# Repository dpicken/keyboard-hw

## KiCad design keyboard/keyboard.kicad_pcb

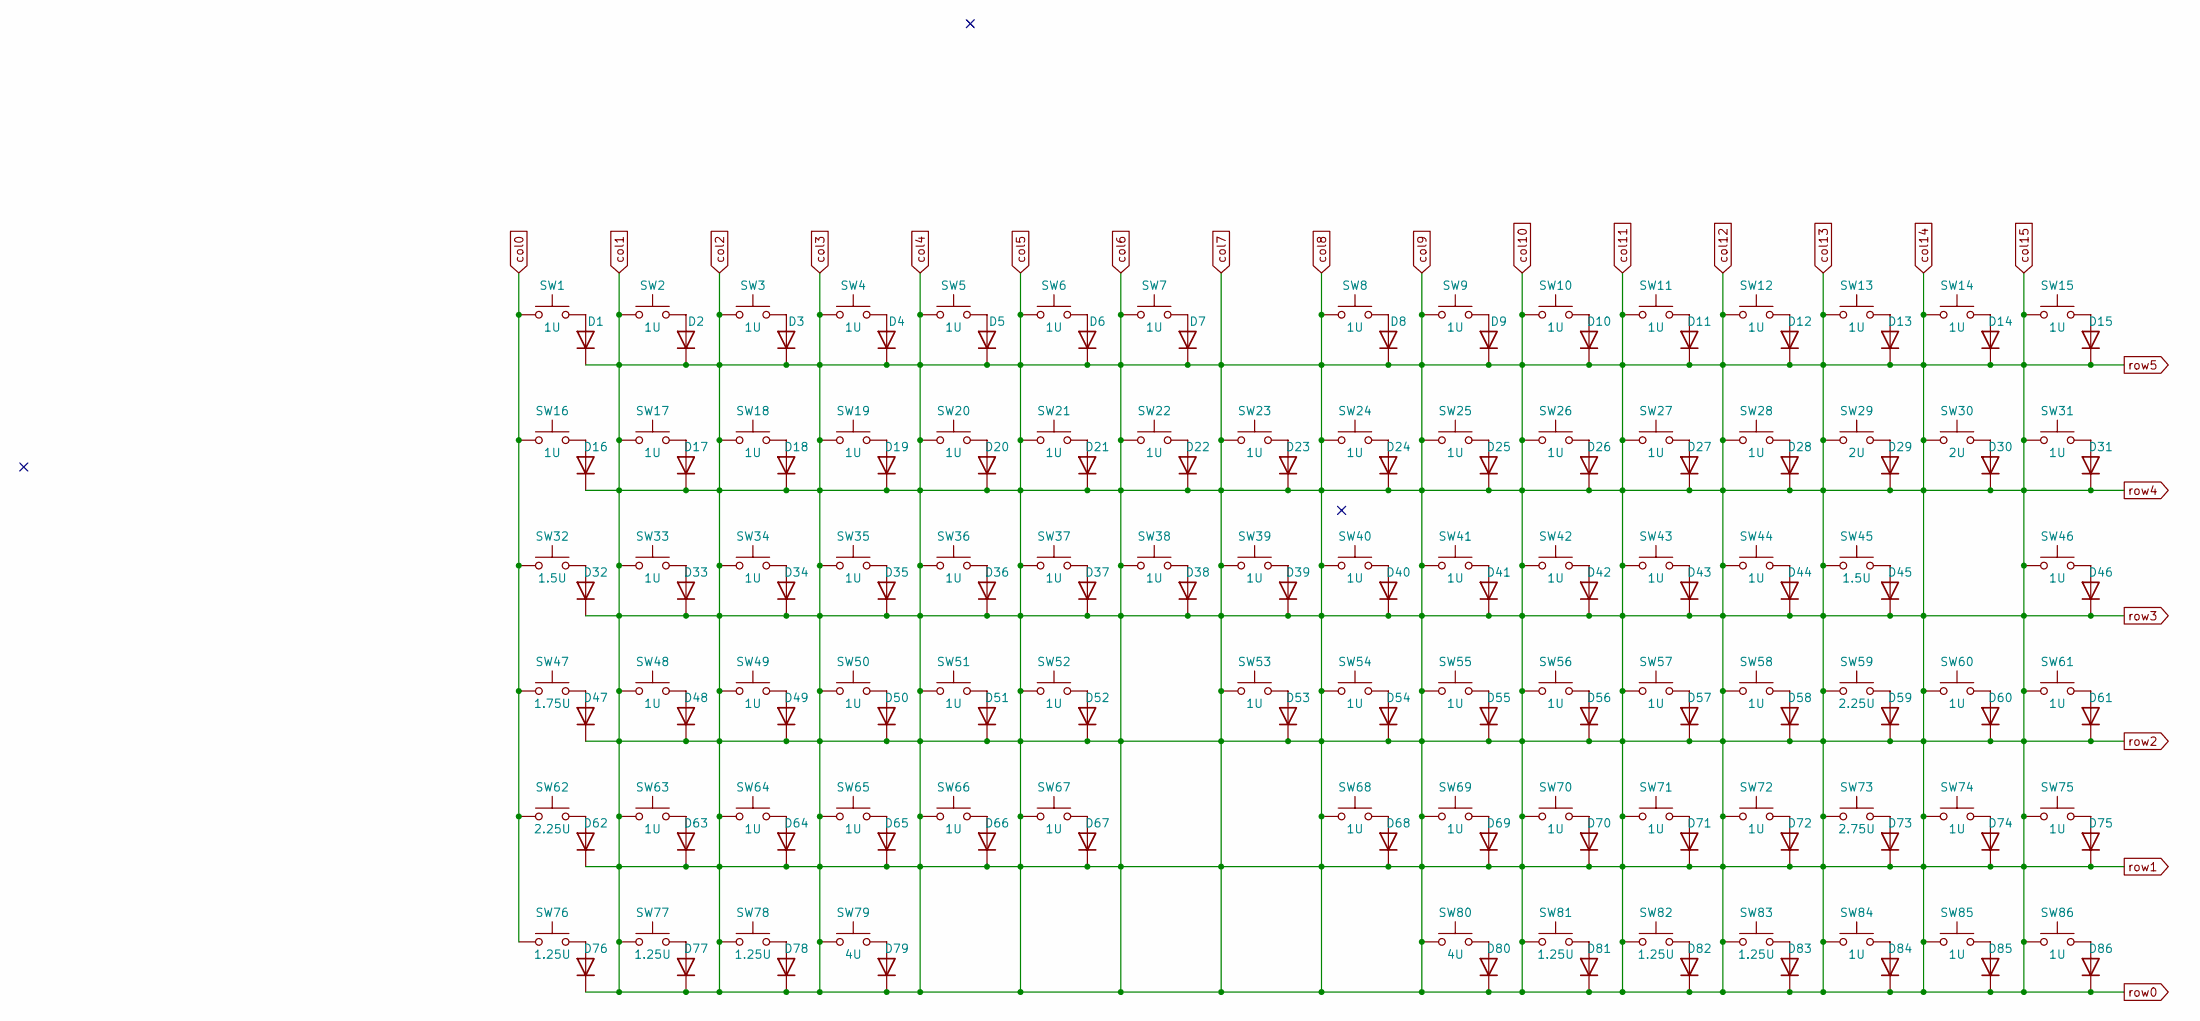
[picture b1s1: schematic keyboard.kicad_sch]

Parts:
D1, D2, D3, D4, D5, D6, D7, D8, D9, D10, D11, D12, D13, D14, D15, D16, D17, D18, D19, D20, D21, D22, D23, D24, D25, D26, D27, D28, D29, D30, D31, D32, D33, D34, D35, D36, D37, D38, D39, D40, D41, D42, D43, D44, D45, D46, D47, D48, D49, D50, D51, D52, D53, D54, D55, D56, D57, D58, D59, D60, D61, D62, D63, D64, D65, D66, D67, D68, D69, D70, D71, D72, D73, D74, D75, D76, D77, D78, D79, D80, D81, D82, D83, D84, D85, D86: 1N4148W; D_SOD-123
SW1, SW2, SW3, SW4, SW5, SW6, SW7, SW8, SW9, SW10, SW11, SW12, SW13, SW14, SW15, SW16, SW17, SW18, SW19, SW20, SW21, SW22, SW23, SW24, SW25, SW26, SW27, SW28, SW31, SW33, SW34, SW35, SW36, SW37, SW38, SW39, SW40, SW41, SW42, SW43, SW44, SW46, SW48, SW49, SW50, SW51, SW52, SW53, SW54, SW55, SW56, SW57, SW58, SW60, SW61, SW63, SW64, SW65, SW66, SW67, SW68, SW69, SW70, SW71, SW72, SW74, SW75, SW84, SW85, SW86: 1U; SW_Hotswap_Kailh_MX_1.00u
SW29, SW30: 2U; SW_Hotswap_Kailh_MX_2.00u
SW32, SW45: 1.5U; SW_Hotswap_Kailh_MX_1.50u
SW47: 1.75U; SW_Hotswap_Kailh_MX_1.75u
SW59, SW62: 2.25U; SW_Hotswap_Kailh_MX_2.25u
SW73: 2.75U; SW_Hotswap_Kailh_MX_2.75u
SW76, SW77, SW78, SW81, SW82, SW83: 1.25U; SW_Hotswap_Kailh_MX_1.25u
SW79, SW80: 4U; SW_Hotswap_Kailh_MX_4.00u

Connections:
unnamed: D1.2 (A), SW1.2
unnamed: D2.2 (A), SW2.2
unnamed: D3.2 (A), SW3.2
unnamed: D4.2 (A), SW4.2
unnamed: D5.2 (A), SW5.2
unnamed: D6.2 (A), SW6.2
unnamed: D7.2 (A), SW7.2
unnamed: D8.2 (A), SW8.2
unnamed: D9.2 (A), SW9.2
unnamed: D10.2 (A), SW10.2
unnamed: D11.2 (A), SW11.2
unnamed: D12.2 (A), SW12.2
unnamed: D13.2 (A), SW13.2
unnamed: D14.2 (A), SW14.2
unnamed: D15.2 (A), SW15.2
unnamed: D16.2 (A), SW16.2
unnamed: D17.2 (A), SW17.2
unnamed: D18.2 (A), SW18.2
unnamed: D19.2 (A), SW19.2
unnamed: D20.2 (A), SW20.2
unnamed: D21.2 (A), SW21.2
unnamed: D22.2 (A), SW22.2
unnamed: D23.2 (A), SW23.2
unnamed: D24.2 (A), SW24.2
unnamed: D25.2 (A), SW25.2
unnamed: D26.2 (A), SW26.2
unnamed: D27.2 (A), SW27.2
unnamed: D28.2 (A), SW28.2
unnamed: D29.2 (A), SW29.2
unnamed: D30.2 (A), SW30.2
unnamed: D31.2 (A), SW31.2
unnamed: D32.2 (A), SW32.2
unnamed: D33.2 (A), SW33.2
unnamed: D34.2 (A), SW34.2
unnamed: D35.2 (A), SW35.2
unnamed: D36.2 (A), SW36.2
unnamed: D37.2 (A), SW37.2
unnamed: D38.2 (A), SW38.2
unnamed: D39.2 (A), SW39.2
unnamed: D40.2 (A), SW40.2
unnamed: D41.2 (A), SW41.2
unnamed: D42.2 (A), SW42.2
unnamed: D43.2 (A), SW43.2
unnamed: D44.2 (A), SW44.2
unnamed: D45.2 (A), SW45.2
unnamed: D46.2 (A), SW46.2
unnamed: D47.2 (A), SW47.2
unnamed: D48.2 (A), SW48.2
unnamed: D49.2 (A), SW49.2
unnamed: D50.2 (A), SW50.2
unnamed: D51.2 (A), SW51.2
unnamed: D52.2 (A), SW52.2
unnamed: D53.2 (A), SW53.2
unnamed: D54.2 (A), SW54.2
unnamed: D55.2 (A), SW55.2
unnamed: D56.2 (A), SW56.2
unnamed: D57.2 (A), SW57.2
unnamed: D58.2 (A), SW58.2
unnamed: D59.2 (A), SW59.2
unnamed: D60.2 (A), SW60.2
unnamed: D61.2 (A), SW61.2
unnamed: D62.2 (A), SW62.2
unnamed: D63.2 (A), SW63.2
unnamed: D64.2 (A), SW64.2
unnamed: D65.2 (A), SW65.2
unnamed: D66.2 (A), SW66.2
unnamed: D67.2 (A), SW67.2
unnamed: D68.2 (A), SW68.2
unnamed: D69.2 (A), SW69.2
unnamed: D70.2 (A), SW70.2
unnamed: D71.2 (A), SW71.2
unnamed: D72.2 (A), SW72.2
unnamed: D73.2 (A), SW73.2
unnamed: D74.2 (A), SW74.2
unnamed: D75.2 (A), SW75.2
unnamed: D76.2 (A), SW76.2
unnamed: D77.2 (A), SW77.2
unnamed: D78.2 (A), SW78.2
unnamed: D79.2 (A), SW79.2
unnamed: D80.2 (A), SW80.2
unnamed: D81.2 (A), SW81.2
unnamed: D82.2 (A), SW82.2
unnamed: D83.2 (A), SW83.2
unnamed: D84.2 (A), SW84.2
unnamed: D85.2 (A), SW85.2
unnamed: D86.2 (A), SW86.2
col0: SW1.1, SW16.1, SW32.1, SW47.1, SW62.1, SW76.1
col1: D1.1 (K), D2.1 (K), D3.1 (K), D4.1 (K), D5.1 (K), D6.1 (K), D7.1 (K), D8.1 (K), D9.1 (K), D10.1 (K), D11.1 (K), D12.1 (K), D13.1 (K), D14.1 (K), D15.1 (K), D16.1 (K), D17.1 (K), D18.1 (K), D19.1 (K), D20.1 (K), D21.1 (K), D22.1 (K), D23.1 (K), D24.1 (K), D25.1 (K), D26.1 (K), D27.1 (K), D28.1 (K), D29.1 (K), D30.1 (K), D31.1 (K), D32.1 (K), D33.1 (K), D34.1 (K), D35.1 (K), D36.1 (K), D37.1 (K), D38.1 (K), D39.1 (K), D40.1 (K), D41.1 (K), D42.1 (K), D43.1 (K), D44.1 (K), D45.1 (K), D46.1 (K), D47.1 (K), D48.1 (K), D49.1 (K), D50.1 (K), D51.1 (K), D52.1 (K), D53.1 (K), D54.1 (K), D55.1 (K), D56.1 (K), D57.1 (K), D58.1 (K), D59.1 (K), D60.1 (K), D61.1 (K), D62.1 (K), D63.1 (K), D64.1 (K), D65.1 (K), D66.1 (K), D67.1 (K), D68.1 (K), D69.1 (K), D70.1 (K), D71.1 (K), D72.1 (K), D73.1 (K), D74.1 (K), D75.1 (K), D76.1 (K), D77.1 (K), D78.1 (K), D79.1 (K), D80.1 (K), D81.1 (K), D82.1 (K), D83.1 (K), D84.1 (K), D85.1 (K), D86.1 (K), SW2.1, SW3.1, SW4.1, SW5.1, SW6.1, SW7.1, SW8.1, SW9.1, SW10.1, SW11.1, SW12.1, SW13.1, SW14.1, SW15.1, SW17.1, SW18.1, SW19.1, SW20.1, SW21.1, SW22.1, SW23.1, SW24.1, SW25.1, SW26.1, SW27.1, SW28.1, SW29.1, SW30.1, SW31.1, SW33.1, SW34.1, SW35.1, SW36.1, SW37.1, SW38.1, SW39.1, SW40.1, SW41.1, SW42.1, SW43.1, SW44.1, SW45.1, SW46.1, SW48.1, SW49.1, SW50.1, SW51.1, SW52.1, SW53.1, SW54.1, SW55.1, SW56.1, SW57.1, SW58.1, SW59.1, SW60.1, SW61.1, SW63.1, SW64.1, SW65.1, SW66.1, SW67.1, SW68.1, SW69.1, SW70.1, SW71.1, SW72.1, SW73.1, SW74.1, SW75.1, SW77.1, SW78.1, SW79.1, SW80.1, SW81.1, SW82.1, SW83.1, SW84.1, SW85.1, SW86.1

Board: 4 copper layers, 172 parts (0 on the bottom side), 88 nets, no tracks yet.

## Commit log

2023-11-29 WIP: Row-staggered, unibody, split keyboard
